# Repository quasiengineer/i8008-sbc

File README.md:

# System board for Intel 8008

Video about this project:

## Board

Schematics in [pdf format](./pcb/schematic.pdf)

Archive with gerber files and drill locations could be found [here](./pcb/manufacturing/manufacturing.zip)

Bill of material in [CSV format](./pcb/i8008-sbc.csv)

|Reference                                            |Value            |Qty|Mouser Part Number  |
|-----------------------------------------------------|-----------------|---|--------------------|
|C4,C5,C6,C7,C8,C9,C13,C15,C20,C21,C22,C23,C24,C25,C26|100n             |15 |187-CL21B104KACNFNC |
|R13,R14,R15,R16,R17,R18,R19,R20,R21,R22,R23,R24      |1k               |12 |603-RT0805FRE071KL  |
|R5,R27,R28,R29,R30,R31,R32,R33,R34                   |220              |9  |603-RT0805FRE10220RL|
|R1,R2,R3,R8,R25,R26                                  |10k              |6  |603-RT0805FRE1310KL |
|U8,U9,U10                                            |CD40109B         |3  |595-CD40109BNSR     |
|U5,U6,U7                                             |LM339_DIP        |3  |595-LM339APWR       |
|C14,C16,C19                                          |1u               |3  |187-CL21B105KOFNNNE |
|R7,R11                                               |30k              |2  |603-RT0805FRE0730KL |
|R4,R6                                                |5k1              |2  |603-RT0805FRE075K1L |
|C17,C18                                              |10u              |2  |810-C2012JB1C106M08C|
|C10,C11                                              |10p              |2  |710-885012007010    |
|C3,C12                                               |4u7              |2  |810-C2012X5R1C475M0B|
|C1,C2                                                |2u2              |2  |187-CL21A225KAFNNNG |
|Y1                                                   |16Mhz            |1  |520-160-10-36CKM-TR3|
|U4                                                   |MP3438           |1  |946-MP3438GTL-P     |
|U3                                                   |LM2937xT         |1  |926-LM2937ET-3.3NOPB|
|U2                                                   |STM32H7A3RGTx    |1  |511-STM32H7A3RGT6   |
|U1                                                   |Intel 8008       |1  |571-1-2199298-5     |
|SW2                                                  |RESET            |1  |667-EVP-AWED4A      |
|SW1                                                  |BOOT             |1  |113-SS3PMVT/R    |
|R12                                                  |2k2              |1  |603-RT0805FRE072K2L |
|R10                                                  |390k             |1  |603-RT0805FRE07390KL|
|R9                                                   |4k7              |1  |603-RT0805FRE074K7L |
|L2                                                   |27n              |1  |652-CE201210-27NJ   |
|L1                                                   |8u2, 800mA       |1  |652-SRR1280-8R2Y    |
|J2                                                   |Type-C           |1  |656-DX07S016JA1R1500|
|FB1                                                  |FerriteBead_Small|1  |652-MH2029-101Y     |
|D2                                                   |Green            |1  |710-150080VS75000   |
|D1                                                   |Red              |1  |710-150080RS75000   |

Also you can find prepared Mouser project [here](https://www.mouser.com/ProjectManager/ProjectDetail.aspx?AccessID=507c82b5f1).

## Firmware

There is compiled [hex file](./firmware/bin/i8008-sbc.hex) in repository, that could be flashed to PCB.

Make sure that `BOOT` switch lever shifted in direction of `RESET` button and connect the board via USB and use stm32 programming software. I am using stm32programmer.

## Software

Make sure that `BOOT` switch lever shifted in direction of stm32 MCU and connect the board via USB.

Red LED should be lighting and new terminal COM device should appear in the system.

To actually run a program in 8008 you just need to run single command:
```sh
node index.js -port=COM5 -rom="programs/blank.i8008"
```

Where `COM5` is the port name. And ROM is the path for program to be run.

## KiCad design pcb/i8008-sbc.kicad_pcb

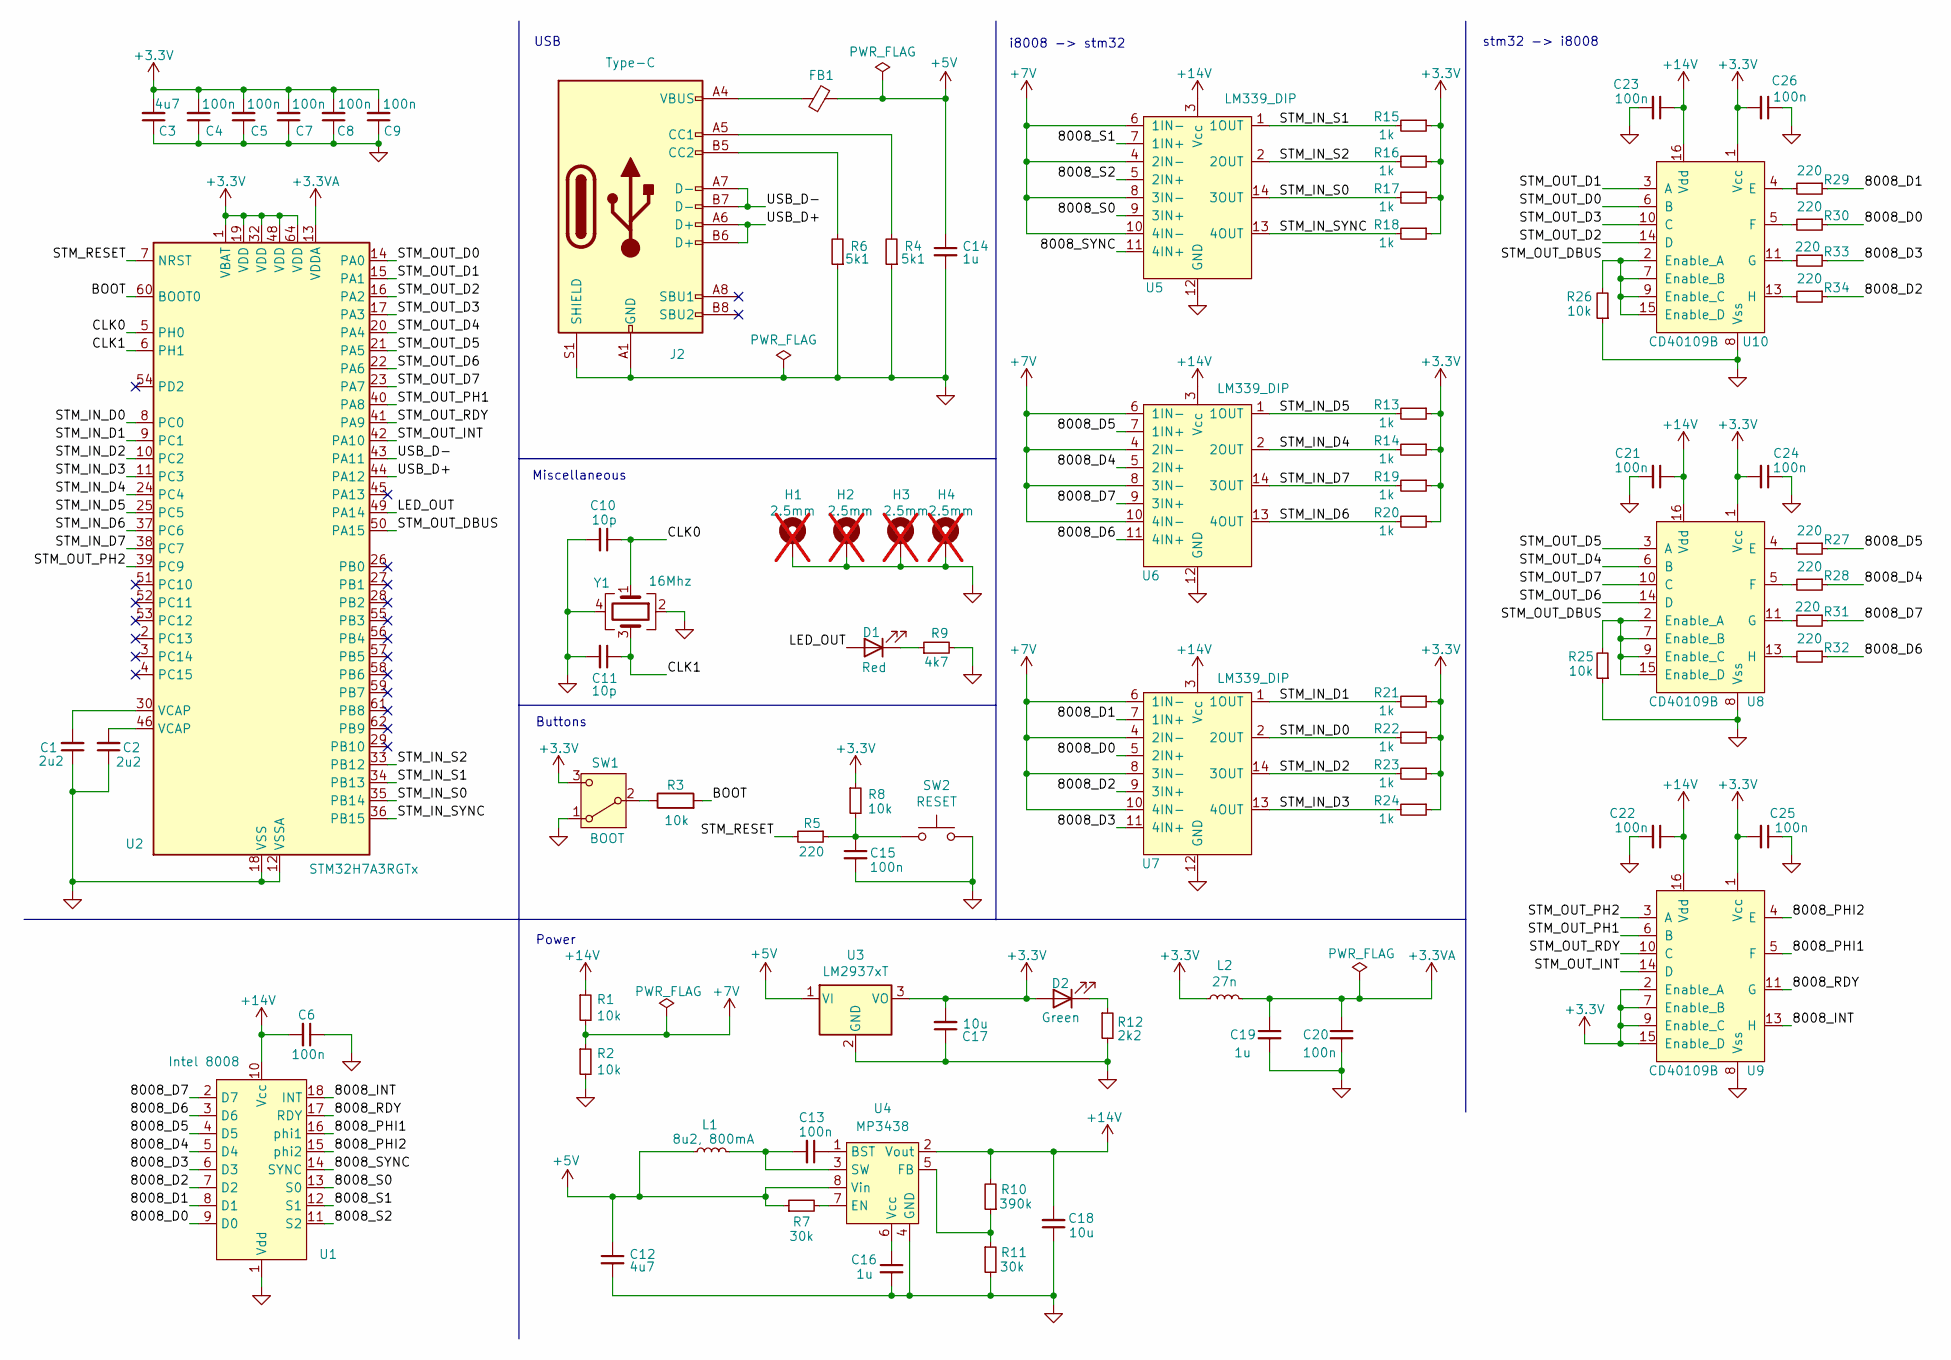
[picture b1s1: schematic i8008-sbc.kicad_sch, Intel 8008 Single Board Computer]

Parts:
C1, C2: 2u2; C_0805_2012Metric_Pad1.18x1.45mm_HandSolder; Mouser Part Number 187-CL21A225KAFNNNG
C3, C12: 4u7; C_0805_2012Metric_Pad1.18x1.45mm_HandSolder; Mouser Part Number 810-C2012X5R1C475M0B
C4, C5, C6, C7, C8, C9, C13, C15, C20, C21, C22, C23, C24, C25, C26: 100n; C_0805_2012Metric_Pad1.18x1.45mm_HandSolder; Mouser Part Number 187-CL21B104KACNFNC
C10, C11: 10p; C_0805_2012Metric_Pad1.18x1.45mm_HandSolder; Mouser Part Number 710-885012007010
C14, C16, C19: 1u; C_0805_2012Metric_Pad1.18x1.45mm_HandSolder; Mouser Part Number 187-CL21B105KOFNNNE
C17, C18: 10u; C_0805_2012Metric_Pad1.18x1.45mm_HandSolder; Mouser Part Number 810-C2012JB1C106M08C
D1: Red; LED_0805_2012Metric_Pad1.15x1.40mm_HandSolder; Mouser Part Number 710-150080RS75000
D2: Green; LED_0805_2012Metric_Pad1.15x1.40mm_HandSolder; Mouser Part Number 710-150080VS75000
FB1: FerriteBead_Small; L_0805_2012Metric_Pad1.15x1.40mm_HandSolder; Mouser Part Number 652-MH2029-101Y
H1, H2, H3, H4: 2.5mm; MountingHole_2.5mm_Pad_Via; not fitted
J2: Type-C; USB_C_Receptacle_JAE_DX07S016JA1R1500; Mouser Part Number 656-DX07S016JA1R1500
L1: 8u2, 800mA; L_1008_2520Metric_Pad1.43x2.20mm_HandSolder; Mouser Part Number 652-SRR1280-8R2Y
L2: 27n; L_0805_2012Metric_Pad1.15x1.40mm_HandSolder; Mouser Part Number 652-CE201210-27NJ
R1, R2, R3, R8, R25, R26: 10k; R_0805_2012Metric_Pad1.20x1.40mm_HandSolder; Mouser Part Number 603-RT0805FRE1310KL
R4, R6: 5k1; R_0805_2012Metric_Pad1.20x1.40mm_HandSolder; Mouser Part Number 603-RT0805FRE075K1L
R5, R27, R28, R29, R30, R31, R32, R33, R34: 220; R_0805_2012Metric_Pad1.20x1.40mm_HandSolder; Mouser Part Number 603-RT0805FRE10220RL
R7, R11: 30k; R_0805_2012Metric_Pad1.20x1.40mm_HandSolder; Mouser Part Number 603-RT0805FRE0730KL
R9: 4k7; R_0805_2012Metric_Pad1.20x1.40mm_HandSolder; Mouser Part Number 603-RT0805FRE074K7L
R10: 390k; R_0805_2012Metric_Pad1.20x1.40mm_HandSolder; Mouser Part Number 603-RT0805FRE07390KL
R12: 2k2; R_0805_2012Metric_Pad1.20x1.40mm_HandSolder; Mouser Part Number 603-RT0805FRE072K2L
R13, R14, R15, R16, R17, R18, R19, R20, R21, R22, R23, R24: 1k; R_0805_2012Metric_Pad1.20x1.40mm_HandSolder; Mouser Part Number 603-RT0805FRE071KL
SW1: BOOT; SS3NPMSVTR; Mouser Part Number 113-SS3PMVT/R
SW2: RESET; EVPAWCD4A; Mouser Part Number 667-EVP-AWED4A
U1: Intel 8008; DIP-18_W7.62mm_Socket; Mouser Part Number 571-1-2199298-5
U2: STM32H7A3RGTx; LQFP-64_10x10mm_P0.5mm; Mouser Part Number 511-STM32H7A3RGT6
U3: LM2937xT; TO-220-3_Vertical; Mouser Part Number 926-LM2937ET-3.3NOPB
U4: MP3438; SOT-583-8; Mouser Part Number 946-MP3438GTL-P
U5, U6, U7: LM339_DIP; TSSOP-14_4.4x5mm_P0.65mm; Mouser Part Number 595-LM339APWR
U8, U9, U10: CD40109B; SO-16_5.3x10.2mm_P1.27mm; Mouser Part Number 595-CD40109BNSR
Y1: 16Mhz; XTAL_ECS-160-10-36-CKM-TR3; Mouser Part Number 520-160-10-36CKM-TR3

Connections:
+3.3V: C3.2, C4.2, C5.2, C7.2, C8.2, C9.2, C17.2, C24.2, C25.2, C26.2, D2.2 (A), L2.1, R8.1, R13.1, R14.1, R15.1, R16.1, R17.1, R18.1, R19.1, R20.1, R21.1, R22.1, R23.1, R24.1, SW1.3 (C), U2.1 (VBAT), U2.19 (VDD), U2.32 (VDD), U2.48 (VDD), U2.64 (VDD), U3.3 (VO), U8.1 (Vcc), U9.1 (Vcc), U9.2 (Enable_A), U9.7 (Enable_B), U9.9 (Enable_C), U9.15 (Enable_D), U10.1 (Vcc)
+3.3VA: C19.1, C20.1, L2.2, U2.13 (VDDA)
+5V: C12.1, C14.1, FB1.2, L1.1, R7.1, U3.1 (VI), U4.8 (Vin)
+7V: R1.2, R2.1, U5.4 (2IN-), U5.6 (1IN-), U5.8 (3IN-), U5.10 (4IN-), U6.4 (2IN-), U6.6 (1IN-), U6.8 (3IN-), U6.10 (4IN-), U7.4 (2IN-), U7.6 (1IN-), U7.8 (3IN-), U7.10 (4IN-)
+14V: C6.2, C18.2, C21.1, C22.1, C23.1, R1.1, R10.2, U1.10 (Vcc), U4.2 (Vout), U5.3 (Vcc), U6.3 (Vcc), U7.3 (Vcc), U8.16 (Vdd), U9.16 (Vdd), U10.16 (Vdd)
/8008_D0: R30.1, U1.9 (D0), U7.5 (2IN+)
/8008_D1: R29.1, U1.8 (D1), U7.7 (1IN+)
/8008_D2: R34.1, U1.7 (D2), U7.9 (3IN+)
/8008_D3: R33.1, U1.6 (D3), U7.11 (4IN+)
/8008_D4: R28.1, U1.5 (D4), U6.5 (2IN+)
/8008_D5: R27.1, U1.4 (D5), U6.7 (1IN+)
/8008_D6: R32.1, U1.3 (D6), U6.11 (4IN+)
/8008_D7: R31.1, U1.2 (D7), U6.9 (3IN+)
/8008_INT: U1.18 (INT), U9.13 (H)
/8008_PHI1: U1.16 (phi1), U9.5 (F)
/8008_PHI2: U1.15 (phi2), U9.4 (E)
/8008_RDY: U1.17 (RDY), U9.11 (G)
/8008_S0: U1.13 (S0), U5.9 (3IN+)
/8008_S1: U1.12 (S1), U5.7 (1IN+)
/8008_S2: U1.11 (S2), U5.5 (2IN+)
/8008_SYNC: U1.14 (SYNC), U5.11 (4IN+)
/BOOT: R3.2, U2.60 (BOOT0)
/CLK0: C10.1, U2.5 (PH0), Y1.1
/CLK1: C11.1, U2.6 (PH1), Y1.3
/LED_OUT: D1.2 (A), U2.49 (PA14)
/STM_IN_D0: R22.2, U2.8 (PC0), U7.2 (2OUT)
/STM_IN_D1: R21.2, U2.9 (PC1), U7.1 (1OUT)
/STM_IN_D2: R23.2, U2.10 (PC2), U7.14 (3OUT)
/STM_IN_D3: R24.2, U2.11 (PC3), U7.13 (4OUT)
/STM_IN_D4: R14.2, U2.24 (PC4), U6.2 (2OUT)
/STM_IN_D5: R13.2, U2.25 (PC5), U6.1 (1OUT)
/STM_IN_D6: R20.2, U2.37 (PC6), U6.13 (4OUT)
/STM_IN_D7: R19.2, U2.38 (PC7), U6.14 (3OUT)
/STM_IN_S0: R17.2, U2.35 (PB14), U5.14 (3OUT)
/STM_IN_S1: R15.2, U2.34 (PB13), U5.1 (1OUT)
/STM_IN_S2: R16.2, U2.33 (PB12), U5.2 (2OUT)
/STM_IN_SYNC: R18.2, U2.36 (PB15), U5.13 (4OUT)
/STM_OUT_D0: U2.14 (PA0), U10.6 (B)
/STM_OUT_D1: U2.15 (PA1), U10.3 (A)
/STM_OUT_D2: U2.16 (PA2), U10.14 (D)
/STM_OUT_D3: U2.17 (PA3), U10.10 (C)
/STM_OUT_D4: U2.20 (PA4), U8.6 (B)
/STM_OUT_D5: U2.21 (PA5), U8.3 (A)
/STM_OUT_D6: U2.22 (PA6), U8.14 (D)
/STM_OUT_D7: U2.23 (PA7), U8.10 (C)
/STM_OUT_DBUS: R25.2, R26.2, U2.50 (PA15), U8.2 (Enable_A), U8.7 (Enable_B), U8.9 (Enable_C), U8.15 (Enable_D), U10.2 (Enable_A), U10.7 (Enable_B), U10.9 (Enable_C), U10.15 (Enable_D)
/STM_OUT_INT: U2.42 (PA10), U9.14 (D)
/STM_OUT_PH1: U2.40 (PA8), U9.6 (B)
/STM_OUT_PH2: U2.39 (PC9), U9.3 (A)
/STM_OUT_RDY: U2.41 (PA9), U9.10 (C)
/STM_RESET: R5.2, U2.7 (NRST)
/USB_D+: J2.A6 (D+), J2.B6 (D+), U2.44 (PA12)
/USB_D-: J2.A7 (D-), J2.B7 (D-), U2.43 (PA11)
GND: C1.1, C2.1, C3.1, C4.1, C5.1, C6.1, C7.1, C8.1, C9.1, C10.2, C11.2, C12.2, C14.2, C15.2, C16.2, C17.1, C18.1, C19.2, C20.2, C21.2, C22.2, C23.2, C24.1, C25.1, C26.1, H1.1, H2.1, H3.1, H4.1, J2.A1 (GND), J2.A12 (GND), J2.B1 (GND), J2.B12 (GND), J2.S1 (SHIELD), R2.2, R4.1, R6.1, R9.2, R11.2, R12.2, R25.1, R26.1, SW1.1 (A), SW2.2, U1.1 (Vdd), U2.12 (VSSA), U2.18 (VSS), U2.31 (VSS), U2.47 (VSS), U2.63 (VSS), U3.2 (GND), U4.4 (GND), U5.12 (GND), U6.12 (GND), U7.12 (GND), U8.8 (Vss), U9.8 (Vss), U10.8 (Vss), Y1.2, Y1.4
unnamed: C1.2, U2.30 (VCAP)
unnamed: C2.2, U2.46 (VCAP)
unnamed: C15.1, R5.1, R8.2, SW2.1
unnamed: D1.1 (K), R9.1
unnamed: D2.1 (K), R12.1
unnamed: FB1.1, J2.A4 (VBUS), J2.A9 (VBUS), J2.B4 (VBUS), J2.B9 (VBUS)
unnamed: J2.A5 (CC1), R4.2
unnamed: J2.B5 (CC2), R6.2
unnamed: R3.1, SW1.2 (B)
unnamed: C13.1, U4.1 (BST)
unnamed: R7.2, U4.7 (EN)
unnamed: R10.1, R11.1, U4.5 (FB)
unnamed: C13.2, L1.2, U4.3 (SW)
unnamed: C16.1, U4.6 (Vcc)
unnamed: R27.2, U8.4 (E)
unnamed: R28.2, U8.5 (F)
unnamed: R31.2, U8.11 (G)
unnamed: R32.2, U8.13 (H)
unnamed: R29.2, U10.4 (E)
unnamed: R30.2, U10.5 (F)
unnamed: R33.2, U10.11 (G)
unnamed: R34.2, U10.13 (H)

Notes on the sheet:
Buttons
i8008 -> stm32
USB
Power
stm32 -> i8008
Miscellaneous

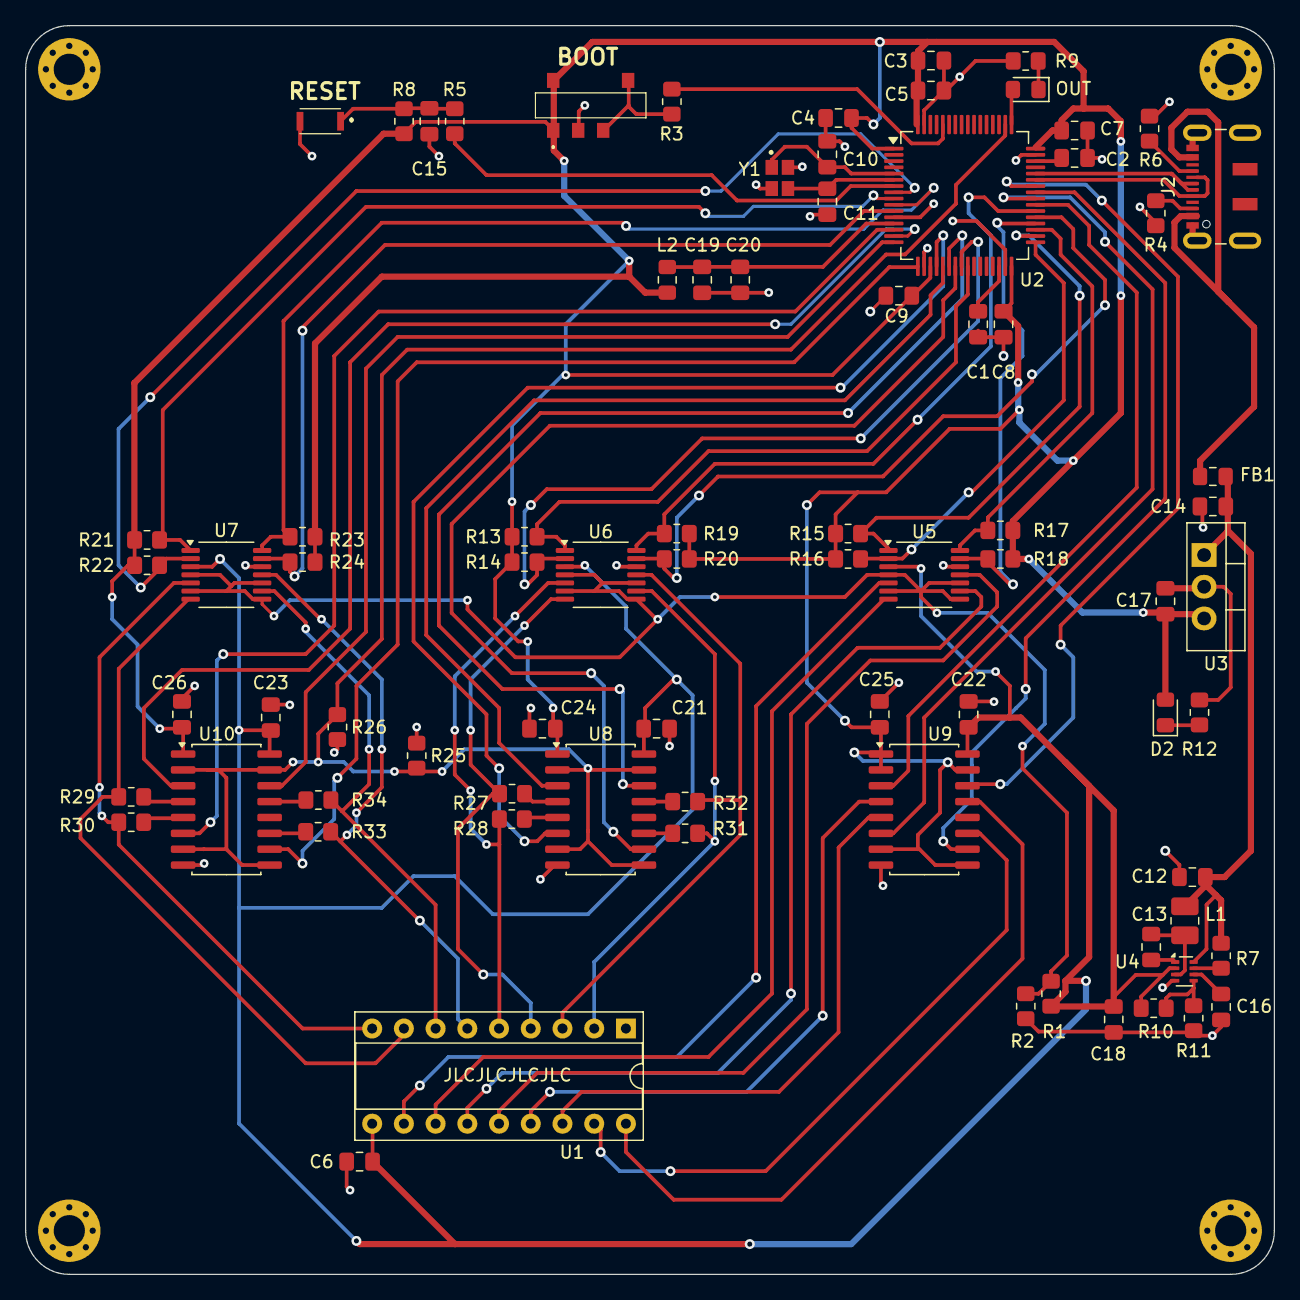
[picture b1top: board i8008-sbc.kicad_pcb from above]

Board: 2 copper layers, 100.0 x 100.0 mm, 83 parts (0 on the bottom side), 76 nets.

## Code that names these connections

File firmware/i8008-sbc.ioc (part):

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Mcu.Name=STM32H7A3R(G-I)Tx
Mcu.Package=LQFP64
Mcu.UserName=STM32H7A3RGTx
PA0.GPIOParameters=GPIO_Label
PA0.GPIO_Label=STM_OUT_D0
PA0.Signal=GPIO_Output
PA1.GPIOParameters=GPIO_Label
PA1.GPIO_Label=STM_OUT_D1
PA1.Signal=GPIO_Output
PA10.GPIOParameters=GPIO_Label
PA10.GPIO_Label=STM_OUT_INT
PA10.Signal=GPIO_Output
PA11.Mode=Device_Only_FS
PA11.Signal=USB_OTG_HS_DM
PA12.Mode=Device_Only_FS
PA12.Signal=USB_OTG_HS_DP
PA14.GPIOParameters=GPIO_Label
PA14.GPIO_Label=LED_OUT
PA14.Signal=GPIO_Output
PA15.GPIOParameters=GPIO_Label
PA15.GPIO_Label=STM_OUT_DBUS
PA15.Signal=GPIO_Output
PA2.GPIOParameters=GPIO_Label
PA2.GPIO_Label=STM_OUT_D2
PA2.Signal=GPIO_Output
PA3.GPIOParameters=GPIO_Label
PA3.GPIO_Label=STM_OUT_D3
PA3.Signal=GPIO_Output
PA4.GPIOParameters=GPIO_Label
PA4.GPIO_Label=STM_OUT_D4
PA4.Signal=GPIO_Output
PA5.GPIOParameters=GPIO_Label
PA5.GPIO_Label=STM_OUT_D5
PA5.Signal=GPIO_Output
PA6.GPIOParameters=GPIO_Label
PA6.GPIO_Label=STM_OUT_D6
PA6.Signal=GPIO_Output
PA7.GPIOParameters=GPIO_Label
PA7.GPIO_Label=STM_OUT_D7
PA7.Signal=GPIO_Output
PA8.GPIOParameters=GPIO_Label
PA8.GPIO_Label=STM_OUT_PH1
PA8.Signal=S_TIM1_CH1
PA9.GPIOParameters=GPIO_Label
PA9.GPIO_Label=STM_OUT_RDY
PA9.Signal=GPIO_Output
PB12.GPIOParameters=GPIO_Label
PB12.GPIO_Label=STM_IN_S2
PB12.Signal=GPIO_Input
PB13.GPIOParameters=GPIO_Label
PB13.GPIO_Label=STM_IN_S1
PB13.Signal=GPIO_Input
PB14.GPIOParameters=GPIO_Label
PB14.GPIO_Label=STM_IN_S0
PB14.Signal=GPIO_Input
PB15.GPIOParameters=GPIO_Label
PB15.GPIO_Label=STM_IN_SYNC
PB15.Signal=GPIO_Input
PB5.GPIOParameters=GPIO_Label
PB5.GPIO_Label=TEST1
PB5.Signal=GPIO_Output
PC0.GPIOParameters=GPIO_Label
PC0.GPIO_Label=STM_IN_D0
PC0.Signal=GPIO_Input
PC1.GPIOParameters=GPIO_Label
PC1.GPIO_Label=STM_IN_D1
PC1.Signal=GPIO_Input
PC2.GPIOParameters=GPIO_Label
PC2.GPIO_Label=STM_IN_D2
PC2.Signal=GPIO_Input
PC3.GPIOParameters=GPIO_Label
PC3.GPIO_Label=STM_IN_D3
PC3.Signal=GPIO_Input
PC4.GPIOParameters=GPIO_Label
PC4.GPIO_Label=STM_IN_D4
PC4.Signal=GPIO_Input
PC5.GPIOParameters=GPIO_Label
PC5.GPIO_Label=STM_IN_D5
PC5.Signal=GPIO_Input
PC6.GPIOParameters=GPIO_Label
PC6.GPIO_Label=STM_IN_D6
PC6.Signal=GPIO_Input
PC7.GPIOParameters=GPIO_Label
PC7.GPIO_Label=STM_IN_D7
PC7.Signal=GPIO_Input
PC9.GPIOParameters=GPIO_Label
PC9.GPIO_Label=STM_OUT_PH2
PC9.Signal=S_TIM8_CH4
PD2.GPIOParameters=GPIO_Label
PD2.GPIO_Label=TEST2
PD2.Signal=GPIO_Output
PH0-OSC_IN.Mode=HSE-External-Oscillator
PH0-OSC_IN.Signal=RCC_OSC_IN
PH1-OSC_OUT.Mode=HSE-External-Oscillator
PH1-OSC_OUT.Signal=RCC_OSC_OUT
RCC.HSE_VALUE=16000000
RCC.SYSCLKFreq_VALUE=280000000
RCC.SYSCLKSource=RCC_SYSCLKSOURCE_PLLCLK
board=custom

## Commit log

2024-05-17 initial
2024-07-22 Add image for youtube link
